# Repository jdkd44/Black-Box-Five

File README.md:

# Black-Box-Five
 2022 Senior Design

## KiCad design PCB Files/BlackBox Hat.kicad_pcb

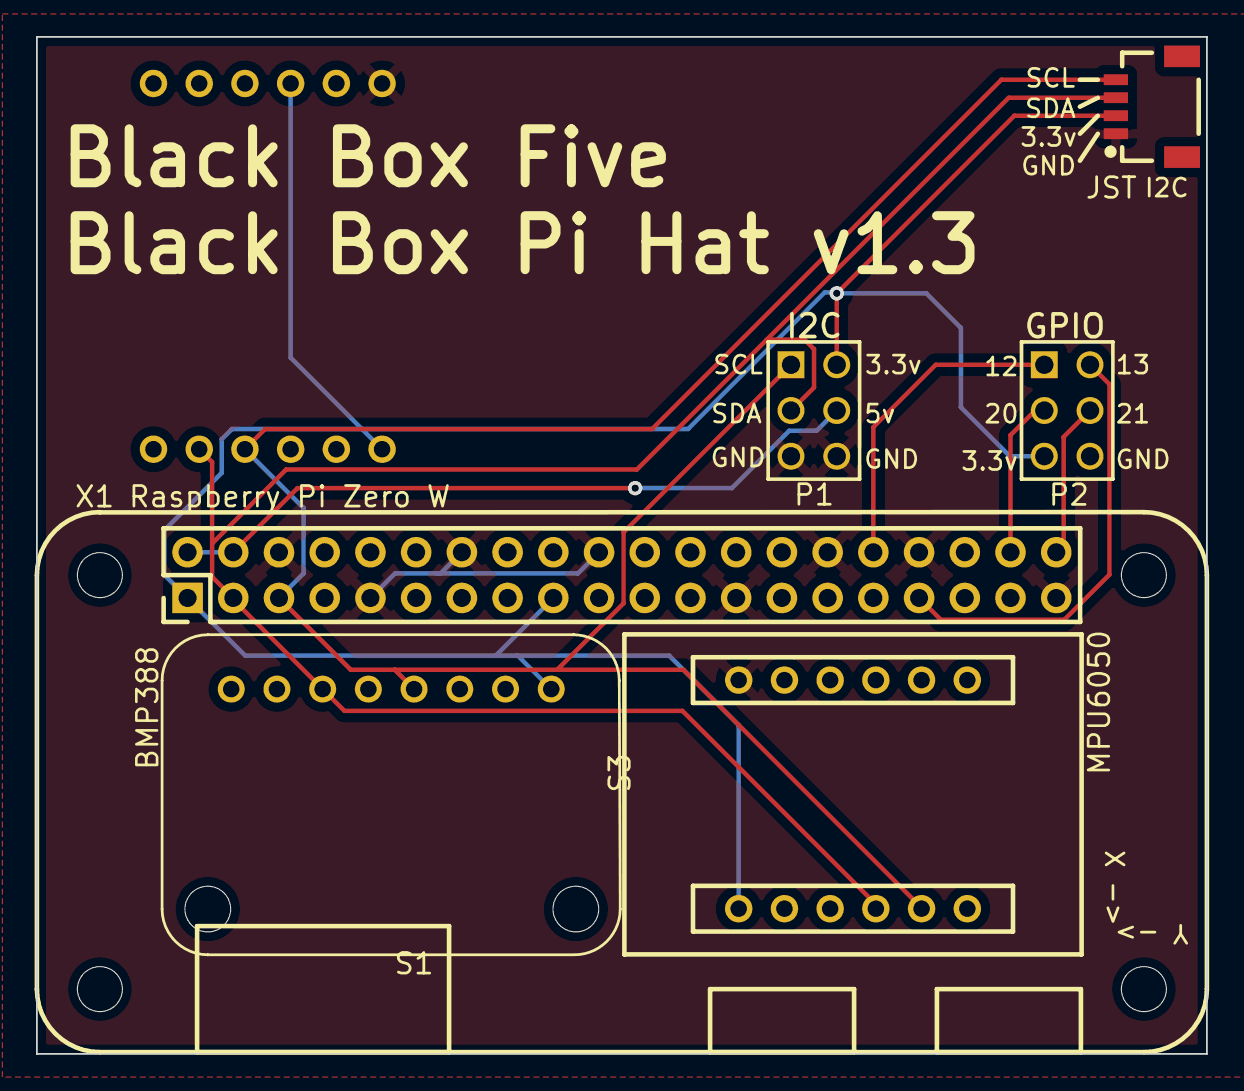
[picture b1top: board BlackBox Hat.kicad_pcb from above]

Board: 2 copper layers, 65.0 x 56.5 mm, 7 parts (1 on the bottom side), 9 nets.

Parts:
JST: I2C; JST SH 4-PIN I2C-H
P1: I2C; 2X3 PIN THROUGH HOLE
P2: GPIO; 2X3 PIN THROUGH HOLE
S1: BMP388; ADAFRUIT BMP388 V2
S3: MPU6050; ADAFRUIT-STEMMAQT-MPU6050
S3#2: PA1010D; ADAFRUIT PA1010D MINI GPS
X1: Raspberry Pi Zero W; RPI_ZERO_W

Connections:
3.3V: JST.2, P1.2, P2.5, S1.1, S3.1, S3#2.3, S3#2.7, X1.1, X1.17
5V: P1.4, X1.2, X1.4
GND: JST.1, P1.5, P1.6, P2.6, S1.3, S3.12, S3#2.1, S3#2.9, X1.6, X1.9, X1.14, X1.20, X1.25, X1.30, X1.34, X1.39
GP12: P2.1, X1.32
GP13: P2.2, X1.33
GP20: P2.3, X1.38
GP21: P2.4, X1.40
SCL: JST.4, P1.1, S1.4, S3.5, S3#2.10, X1.5
SDA: JST.3, P1.3, S1.6, S3.4, S3#2.11, X1.3

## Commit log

2022-01-28 initalize folders
2022-01-28 Create new Doc
2022-01-28 created index.html
2022-01-30 PCB Designed
2022-02-07 PCB Drill Files Added
2022-02-07 Web GUI Beginnings
    -Created python virtual environment
    -Created basic website
2022-02-08 Database created
    -logging programs written
    -directories rearranged
    -website UI redone, still needs finishing
2022-02-08 Code Directories Cleaned up
2022-02-14 Removed seperate webUI folder for ease of testing
2022-02-14 Created main.py
    main.py contains getting data, logging data, and hosting webpage in one file.
    Needed so that data can be passed between webpage and database. Also allows for logging speed to be adjusted by the web UI. Mainly just created for a setup
2022-02-16 Database reformatted, web framework added
    -Database reworked to hopefully reduce file size
    -intercooler.js added for refreshing data on webpage easier
    -python cleaned up a little bit
2022-02-16 fixed 2 typos
2022-02-17 Export functionality added and directory cleaned up
2022-02-21 Improved data passage from database to webpage
    -added /data and /chart for passing data from database to webpage
    -Renamed variables for better consistency
2022-02-21 Webpage Template Created
2022-02-21 Reworked flask database query function
    returns json that is able to be queried by chart.js more easily
2022-02-21 fixed error in database parse rework
2022-02-21 added forgotten database closing code
2022-02-22 reverting changed json formatting
    i goofed in the previous ones lmao
2022-02-22 make website less bad
2022-02-25 CanvasJS files added,
2022-02-28 made it easier to transfer python virtual environment across pcs
2022-02-28 Installed libraries for sensors
2022-03-01 Update virtual environment instructions
2022-03-01 Webpage Improvements
    -Added webpage CSV export download
    -somewhat fixed the charts
    -added settings panel and battery level
2022-03-02 fix for unknown urls
2022-03-07 Removed KiCad blackups
2022-03-08 webpage charting works
    updates and logs too quick
2022-03-09 things almost working again
2022-03-09 Added some sensor reading code and updated libraries that needed updating
2022-03-09 data logging working, needs polling rate changing
2022-03-09 cleaned up updateGUI()
2022-03-09 added shutdown
2022-03-09 Fixed data logging
2022-03-09 Added faux sensor read file testsensorRead.py
2022-03-09 oled status updating
2022-03-10 improved webpage chart loading on load
2022-03-10 actually improved webpage chart loading on load
2022-04-08 Edit oled update logic
2022-04-10 Added more sensor read code
2022-04-24 Code updates for running on pi
2022-04-25 condensed code
2022-04-25 add support for no GPS satellite connection
2022-04-25 battery reading support
2022-04-25 Added PiSugar2 battery API
2022-04-25 update for accelerometer support
2022-04-25 cleanup
2022-04-25 condense
2022-04-26 fix database
2022-04-26 make acceleration work
2022-04-26 Fix database export
2022-04-27 update gps interactions
2022-04-27 gps fix, no velocity data
2022-04-28 code cleanup
2022-04-30 possible code fix
2022-04-30 database update
2022-04-30 debugging
2022-04-30 bugfixes
2022-04-30 formatting
2022-05-03 Final release (minus OLED support)
2022-05-03 formatting and cleanup
2022-05-10 Final Version
2022-05-11 Add STEP file for Hat
2022-05-11 Add case CAD
2022-05-12 Final Repository Cleanup
2022-05-12 Finalize Cleanup
